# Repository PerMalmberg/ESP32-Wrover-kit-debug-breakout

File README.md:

# ESP32-Wrover-kit-debug-breakout
Breakout board for JTAG and UART for the ESP32 Wrover kit

DXF of Wrover-kit is provided and copyrighted by [Espressif](https://www.esp32.com/viewtopic.php?f=2&t=6686).

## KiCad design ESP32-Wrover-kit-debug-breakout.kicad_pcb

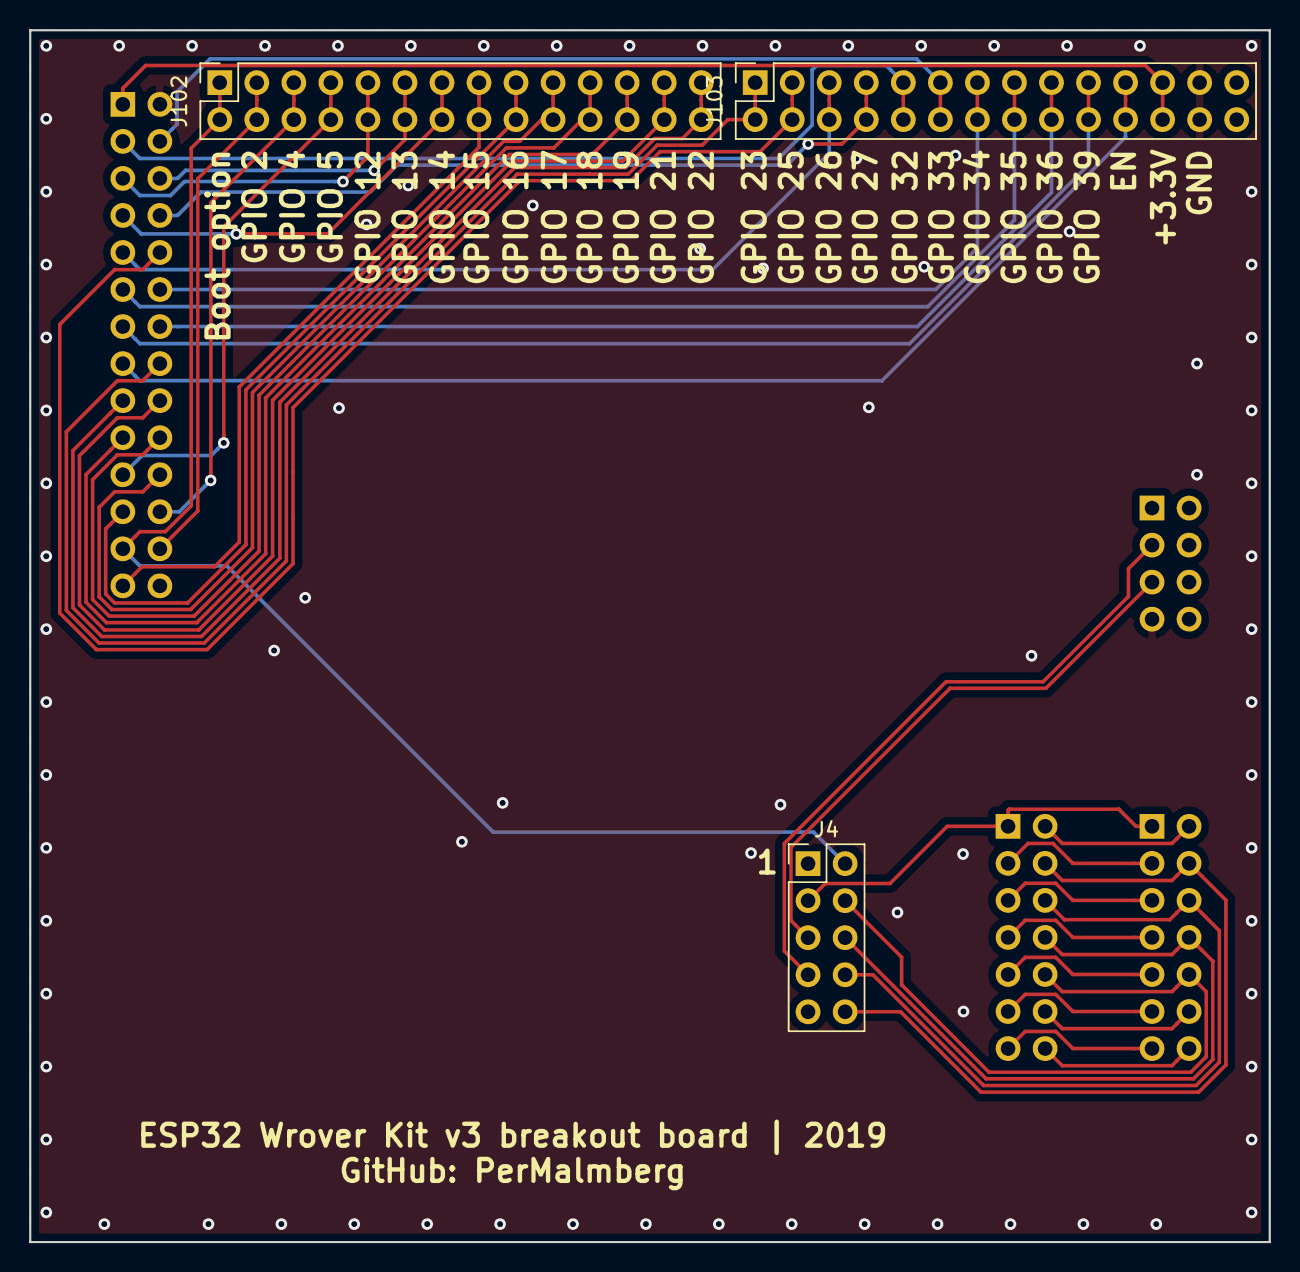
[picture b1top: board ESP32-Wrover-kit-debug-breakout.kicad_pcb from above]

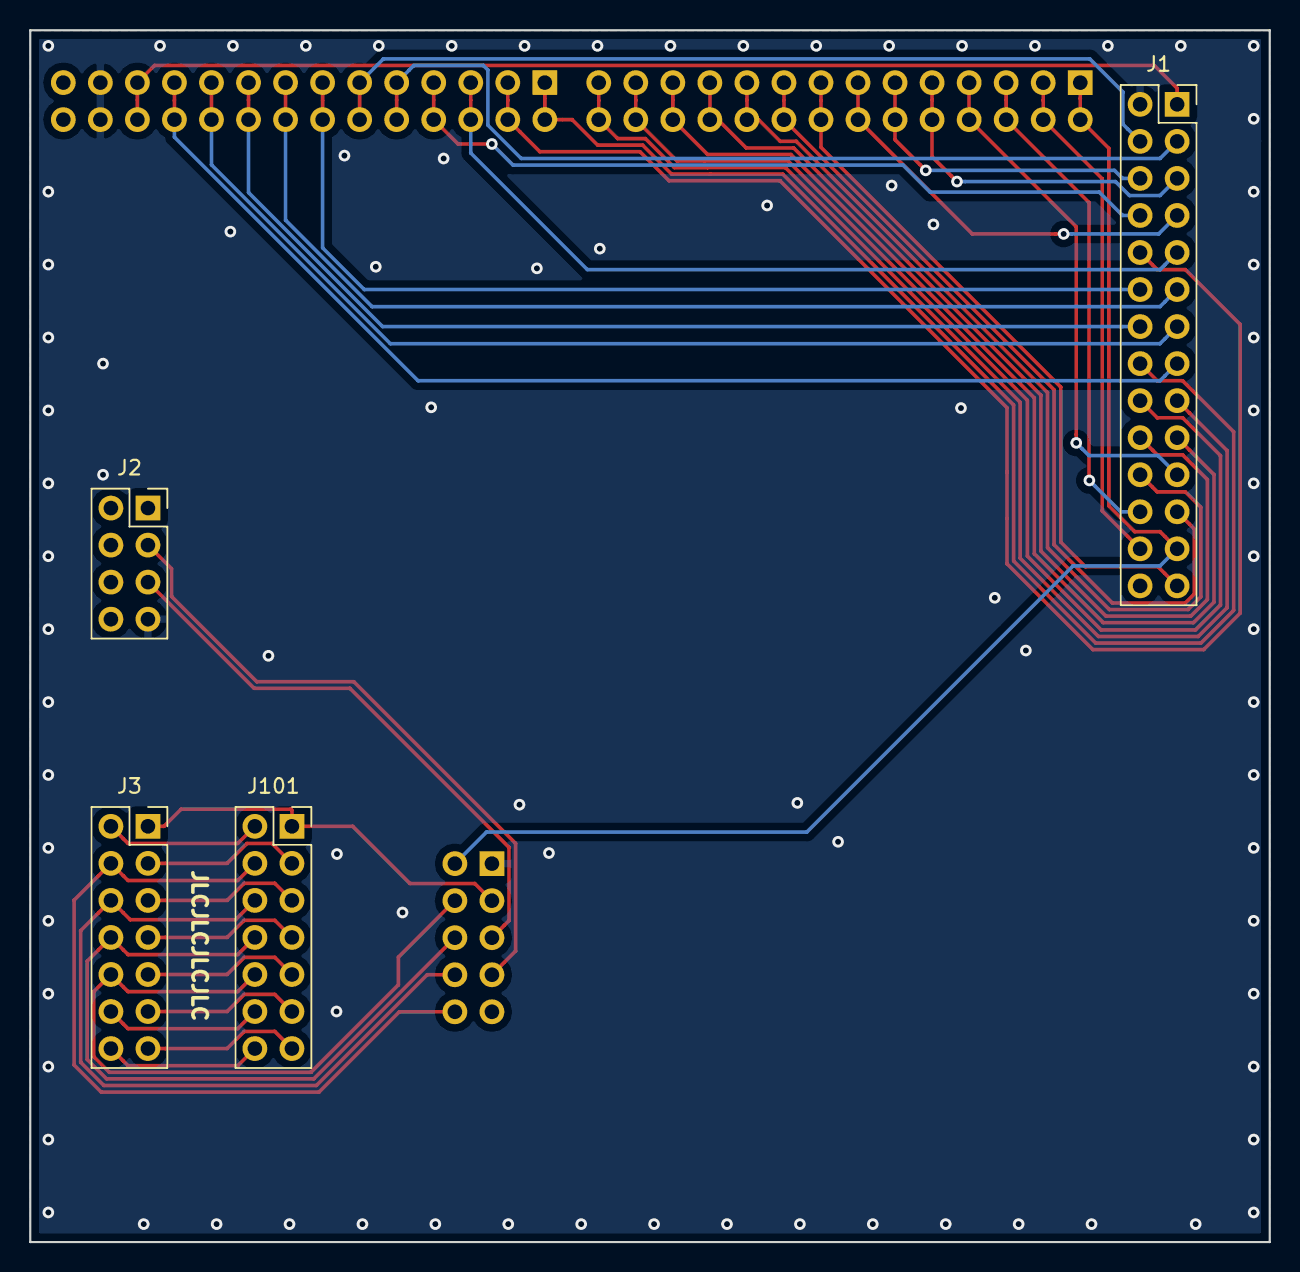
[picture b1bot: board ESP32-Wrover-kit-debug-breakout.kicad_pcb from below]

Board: 2 copper layers, 85.0 x 83.1 mm, 7 parts (4 on the bottom side), 43 nets.

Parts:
J1, J102, J103: Conn_02x14_Odd_Even; PinSocket_2x14_P2.54mm_Vertical
J2: Conn_02x04_Odd_Even; PinSocket_2x04_P2.54mm_Vertical
J3, J101: Conn_02x07_Odd_Even; PinSocket_2x07_P2.54mm_Vertical
J4: Conn_02x05_Odd_Even; PinHeader_2x05_P2.54mm_Vertical

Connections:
+3V3: J1.1, J103.23, J103.24
/CH_Enable: J3.1, J4.3, J101.1
/EN: J1.15, J103.21, J103.22
/GPIO_2: J1.26, J102.3, J102.4
/GPIO_4: J1.24, J102.5, J102.6
/GPIO_5: J1.21, J102.7, J102.8
/GPIO_12: J1.5, J102.9, J102.10
/GPIO_13: J1.6, J102.11, J102.12
/GPIO_14: J1.7, J102.13, J102.14
/GPIO_15: J1.27, J102.15, J102.16
/GPIO_16: J1.23, J102.17, J102.18
/GPIO_17: J1.22, J102.19, J102.20
/GPIO_18: J1.20, J102.21, J102.22
/GPIO_19: J1.19, J102.23, J102.24
/GPIO_21: J1.18, J102.25, J102.26
/GPIO_22: J1.17, J102.27, J102.28
/GPIO_23: J1.16, J103.1, J103.2
/GPIO_25: J1.10, J103.3, J103.4
/GPIO_26: J1.9, J103.5, J103.6
/GPIO_27: J1.8, J103.7, J103.8
/GPIO_32: J1.3, J103.9, J103.10
/GPIO_33: J1.4, J103.11, J103.12
/GPIO_34: J1.12, J103.13, J103.14
/GPIO_35: J1.11, J103.15, J103.16
/GPIO_36: J1.14, J103.17, J103.18
/GPIO_39: J1.13, J103.19, J103.20
/IO0_Boot_option: J1.25, J4.2, J102.1, J102.2
/MTCK: J3.10, J4.4, J101.10
/MTDI: J3.8, J4.6, J101.8
/MTDO: J3.6, J4.8, J101.6
/MTMS: J3.4, J4.10, J101.4
/RDX: J2.3, J4.7
/TDX: J2.5, J4.5
GND: J1.2, J2.7, J4.1, J103.25, J103.26
unnamed: J3.2, J101.2
unnamed: J3.3, J101.3
unnamed: J3.5, J101.5
unnamed: J3.7, J101.7
unnamed: J3.9, J101.9
unnamed: J3.11, J101.11
unnamed: J3.12, J101.12
unnamed: J3.13, J101.13
unnamed: J3.14, J101.14

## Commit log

2018-09-09 Schematics and PCB layout.
2018-09-09 Added Zip with DXF of wrover kit
2018-09-10 RX/TX name change
2018-09-23 Updated locations of headers.
2018-09-25 Text adjustements. Added PCB manufacturing files.
2018-10-11 Fixed schematics. Closes #1. Closes #2
2018-10-14 #2 Move JTAG signals to correct pin.
2018-10-14 #2 It is acutally the Chip Enable signal we want, not nSRST since the enable signal is pulled low by the flasher.
2018-11-17 Update PCB manufacturing files.
2018-11-17 Removed OSHW logo from schematics file.
2019-01-10 Added soldering pads for IOs
2019-01-21 Updated production files.
2019-01-23 Added markers for GPIO.
